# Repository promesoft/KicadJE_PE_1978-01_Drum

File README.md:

# KicadJE_PE_1978-01_Drum
Based on https://worldradiohistory.com/UK/Practical-Electronics/70s/Practical-Electronics-1978-01.pdf

# Purpose

## Board 1 - Drum module
Adjustment:  
Mix of snare amt

Gate Input:  
TTL Square

Output Audio:  
+/- 10V AC coupled

## Board 2 - Breadboard helper
Testing out text prints

Adjustment:  
100k Pot to pinheader  
Push button to pinheader

Input/Output:  
3,5mm jack to pinheader  
+-12V from Eurorack 10pin IDC to breadboard pinheaders

## Board 3 - Desktop PDU for Eurojack
Banana jack in  
16 pin Euro power out

# Status - Being assembled
## Initial 
| Stage  | Detail | Status |
| ------------- | ------------- | ------------- |
| create material  | sch | done |
| | pcb | done |
| | gerber | done |
| production  |   | delivered |
|  | produced | delivered |
|  | delivered | ok |
## Preliminary validation
| Test  | Detail | Status |
| ------------- | ------------- | ------------- |
| Initial Inspection | PDU | ok mechanical|
| Initial Inspection | BB Helper | ok mechanical - Solder-mask-expansion on copper looks best - better than silk |
| Initial Inspection | Drum Module |  |
| Initial Technical Test | Board 1 |  |
| Initial Product Test | Board1 |  |

## Secondary validation
| Test  | Detail | Status |
| ------------- | ------------- |------------- |
| Product Test | 1 | |
| Quality | 1 | |
| Long Term Product Test |  |  |
| Power Draw |  | 

## Errata
### Errata - BB Power
### Errata - PDU
R405 not connected to GND

## Issues and Notes
### 

# Pictures

# Schematic
## Sch 1

# Analysis
## Diag 1

https://worldradiohistory.com/UK/Practical-Electronics/70s/Practical-Electronics-1978-01.pdf

## Prototype

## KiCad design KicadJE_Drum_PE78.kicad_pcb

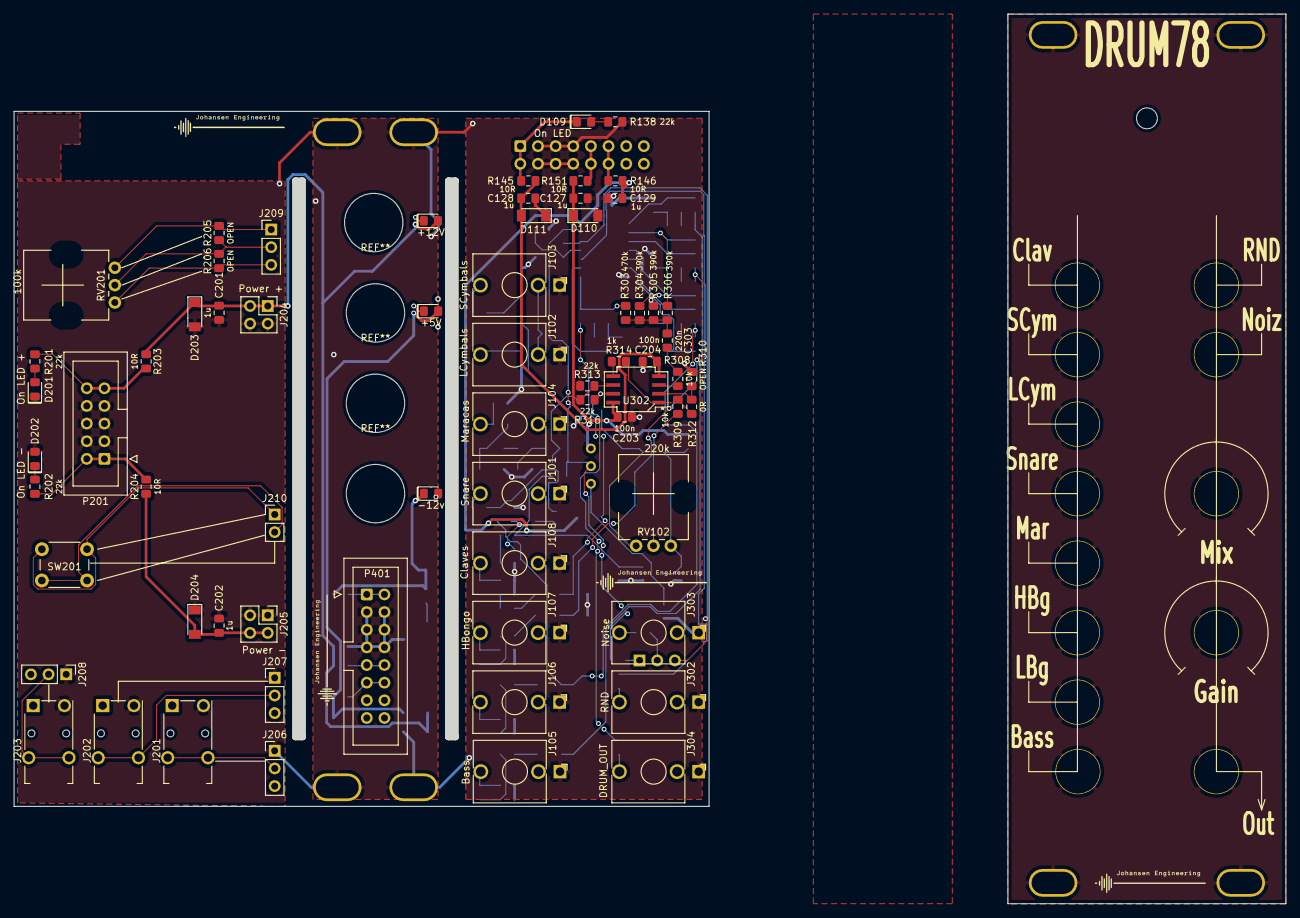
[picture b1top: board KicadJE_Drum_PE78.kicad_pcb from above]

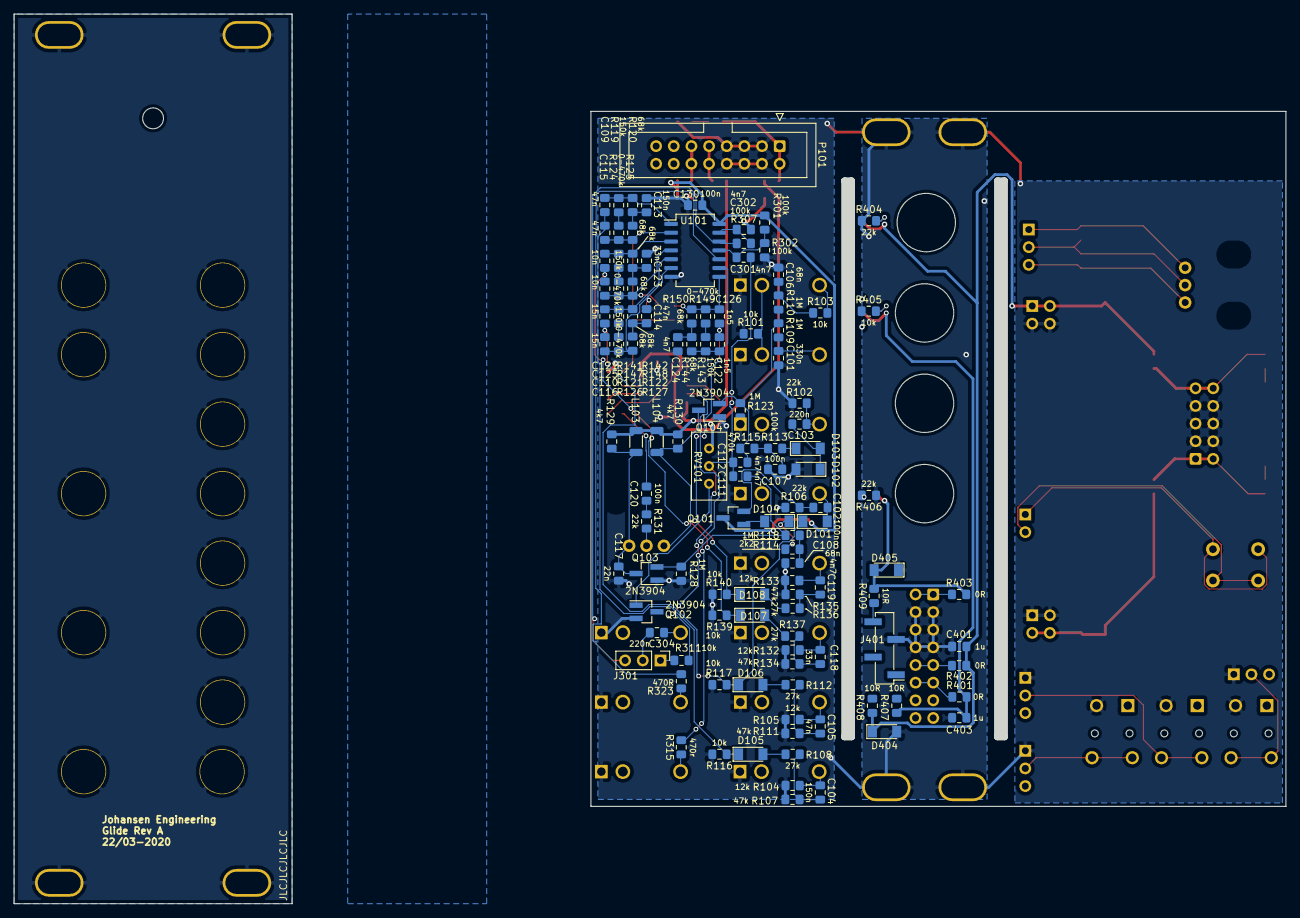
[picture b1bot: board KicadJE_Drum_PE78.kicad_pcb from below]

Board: 2 copper layers, 100.0 x 100.0 mm, 203 parts (121 on the bottom side), 100 nets.

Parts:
C101: 330n; C_0805_AJ
C102, C107, C120, C130, C203, C204: 100n; C_0805_AJ
C103, C303, C304: 220n; C_0805_AJ
C104, C113: 150n; C_0805_AJ
C105, C109, C114, C115: 47n; C_0805_AJ
C106, C108: 68n; C_0805_AJ
C110, C116: 15n; C_0805_AJ
C111, C112, C119, C124, C301, C302: 4n7; C_0805_AJ
C117: 22n; C_0805_AJ
C118, C123: 33n; C_0805_AJ
C121, C125: 10n; C_0805_AJ
C122, C126: 1n5; C_0805_AJ
C127, C128, C129, C201, C202, C401, C403: 1u; C_0805_AJ
D101, D102, D103, D104, D105, D106, D107, D108: 1N4148; D_MiniMELF
D109: On LED; D_0805_AJ
D110, D111, D203, D204, D404, D405: 1N4007; D_MiniMELF
D201: On LED +; D_0805_AJ
D202: On LED -; D_0805_AJ
D401: +12V; D_0805_AJ
D402: +5V; D_0805_AJ
D403: -12v; D_0805_AJ
H101: ON; LED_Hole_3mm
H102, H103, H103#2, H103#3, H103#4, H103#5, H104, H105: MountingHole_Pad; MountingHole_Eurorack3
J101: Snare; Jack_3.5mm_QingPu_WQP-PJ398SM_Vertical_CircularHoles
J102: LCymbals; Jack_3.5mm_QingPu_WQP-PJ398SM_Vertical_CircularHoles
J103: SCymbals; Jack_3.5mm_QingPu_WQP-PJ398SM_Vertical_CircularHoles
J104: Maracas; Jack_3.5mm_QingPu_WQP-PJ398SM_Vertical_CircularHoles
J105: Bass; Jack_3.5mm_QingPu_WQP-PJ398SM_Vertical_CircularHoles
J106: LBongo; Jack_3.5mm_QingPu_WQP-PJ398SM_Vertical_CircularHoles
J107: HBongo; Jack_3.5mm_QingPu_WQP-PJ398SM_Vertical_CircularHoles
J108: Claves; Jack_3.5mm_QingPu_WQP-PJ398SM_Vertical_CircularHoles
J201, J202, J203: AudioJack2_SwitchT; Jack_3.5mm_Switronic_ST-005-G_horizontal
J204: Power +; PinHeader_2x02_P2.54mm_Vertical
J205: Power -; PinHeader_2x02_P2.54mm_Vertical
J206, J207, J208, J209: Conn_01x03_Male; PinHeader_1x03_P2.54mm_Vertical
J210: Conn_01x02_Male; PinHeader_1x02_P2.54mm_Vertical
J301: Tone/Noise; PinHeader_1x03_P2.54mm_Vertical
J302: RND; Jack_3.5mm_QingPu_WQP-PJ398SM_Vertical_CircularHoles
J303: Noise; Jack_3.5mm_QingPu_WQP-PJ398SM_Vertical_CircularHoles
J304: DRUM_OUT; Jack_3.5mm_QingPu_WQP-PJ398SM_Vertical_CircularHoles
J401: Tone/Noise; PinHeader_1x04_P2.54mm_Vertical_SMD_Pin1Left
L103, L104: 100mH; L_1206_3216Metric
P101, P401: HEADER_2x8_Doepfer; IDC-Header_2x08_P2.54mm_Vertical
P201: HEADER_2x5_Doepfer; IDC-Header_2x05_P2.54mm_Vertical
Q101, Q102, Q103, Q104: 2N3904; SOT-23_Handsoldering
R101, R103, R116, R117, R139, R140, R308, R309, R311, R405: 10k; R_0805_AJ
R102, R106, R131, R138, R201, R202, R313, R316, R404, R406: 22k; R_0805_AJ
R104, R105, R132, R133: 12k; R_0805_AJ
R107, R108, R134, R135: 47k; R_0805_AJ
R109, R110, R118, R123, R128: 1M; R_0805_AJ
R111, R112, R136, R137: 27k; R_0805_AJ
R113, R301, R302, R307: 100k; R_0805_AJ
R114: 2k2; R_0805_AJ
R115, R303: 470k; R_0805_AJ
R119, R121, R141, R143: 150k; R_0805_AJ
R120, R122, R125, R127, R142, R144, R148, R150: 68k; R_0805_AJ
R124, R126, R147, R149: 0-470k; R_0805_AJ
R129, R130: 4k7; R_0805_AJ
R145, R146, R151, R203, R204, R407, R408, R409: 10R; R_0805_AJ
R205, R206, R310: OPEN; R_0805_AJ
R304, R305, R306: 390k; R_0805_AJ
R312, R401, R402, R403: 0R; R_0805_AJ
R314: 1k; R_0805_AJ
R315: 470r; R_0805_AJ
R323: 470R; R_0805_AJ
RV101: R_POT_TRIM; Potentiometer_Bourns_3296W_Vertical
RV102: 220k; Potentiometer_China_RK09_Single_Vertical_AJ
RV201: 100k; Potentiometer_China_RK09_Single_Vertical_AJ
SW201: SW_SPDT; SW_PUSH_6mm_H8mm
TP102: SQ; Jack_6m3
TP103: In1; Jack_6m3
TP105, TP105#2, TP105#3, TP105#4, TP105#5, TP105#6: In3; Jack_6m3
TP106: HS; Jack_6m3
TP107: OFF1; Pot_6m3_scale1
TP107#2: FM; Jack_6m3
TP108: PWM; Jack_6m3
TP112: Fine; Pot_6m3_scale1
U101: 74HC04; SO-14_5.3x10.2mm_P1.27mm
U302: TL072; AJ_SO-8_5.3x6.2mm_P1.27mm

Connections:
+5V: C129.1, C130.1, C403.1, D402.2, Q101.3, R146.1, R301.1, R401.2, R407.2, U101.14
+12Vc: C127.1, C201.1, C203.1, C401.1, D110.1, D203.1, D401.2, D404.1, J204.1, J204.3, L103.1, L104.1, R129.2, R130.2, R151.1, R203.1, R402.2, R408.2, RV101.1, U302.8
-12Vc: C128.2, C202.2, C204.2, D111.2, D204.2, D403.1, D405.2, J205.2, J205.4, R145.1, R204.1, R403.2, R409.2, U302.4
/+5: P101.11, P101.12, R146.2
/+12: P101.9, P101.10, R151.2
/-12: D109.1, P101.1, P101.2, R145.2
/Breadboard_extender/+12: P201.9, P201.10, R201.1, R203.2
/Breadboard_extender/-12: P201.1, P201.2, R202.1, R204.2
/KicadJE_PDU_1/+5: P401.11, P401.12, R401.1
/KicadJE_PDU_1/+12: P401.9, P401.10, R402.1
/KicadJE_PDU_1/-12: P401.1, P401.2, R403.1
BassOut: C115.1, R124.1, R125.1, R306.2, U101.2
BassTrig: C109.1, C115.2, D105.1, R116.1
ClavesOut: C126.1, R149.1, R150.1, R303.2, U101.8
ClavesTrig: C122.1, C126.2, D108.1, R140.1
GND: C101.2, C106.2, C107.2, C108.2, C113.2, C114.2, C117.2, C123.2, C124.2, C127.2, C128.1, C129.2, C130.2, C201.2, C202.1, C203.2, C204.1, C302.1, C401.2, C403.2, D102.2, D110.2, D111.1, D201.1, D202.2, D203.2, D204.1, D404.2, D405.1, H102.1, H103.1, H103#2.1, H103#3.1, H103#4.1, H103#5.1, H104.1, H105.1, J101.S, J102.S, J103.S, J104.S, J105.S, J106.S, J107.S, J108.S, J201.S, J202.S, J203.S, J204.2, J204.4, J205.1, J205.3, J206.1, J207.1, J208.1, J302.S, J303.S, J304.S, J401.3, P101.3, P101.4, P101.5, P101.6, P101.7, P101.8, P201.3, P201.4, P201.5, P201.6, P201.7, P201.8, P401.3, P401.4, P401.5, P401.6, P401.7, P401.8, Q102.2, Q103.1, Q104.1, R101.1, R102.2, R104.2, R105.2, R106.2, R107.2, R108.2, R116.2, R117.2, R123.1, R128.1, R132.2, R133.2, R134.2, R135.2, R138.1, R139.2, R140.2, R302.2, R310.2, R313.1, R404.1, R405.1, R406.1, TP102.1, TP103.1, TP105.1, TP105#2.1, TP105#3.1, TP105#4.1, TP105#5.1, TP105#6.1, TP106.1, TP107.1, TP107#2.1, TP108.1, TP112.1, U101.7
HBongoOut: C125.1, R147.1, R148.1, R304.2, U101.4
HBongoTrig: C121.1, C125.2, D107.1, R139.1
LBongoOut: C116.1, R126.1, R127.1, R305.2, U101.6
LBongoTrig: C110.1, C116.2, D101.1, D106.1, R117.1
NDrumsOut: C120.2, R309.2
unnamed: C101.1, J102.T, R109.2
unnamed: C102.1, D101.2, J101.T
unnamed: C102.2, Q101.2, R106.1
unnamed: C103.1, J104.T, R102.1
unnamed: C103.2, D102.1, D103.2
unnamed: C104.1, J105.T, R104.1
unnamed: C104.2, R107.1, R111.2
unnamed: C105.1, J106.T, R105.1
unnamed: C105.2, R108.1, R112.2
unnamed: C106.1, R103.1, R110.2
unnamed: C107.1, R113.1, R115.2
unnamed: C108.1, R114.1, R118.2
unnamed: C109.2, R119.2, R120.2, U101.1
unnamed: C110.2, R121.2, R122.2, U101.5
unnamed: C111.2, Q103.2, R118.1, R128.2
unnamed: C112.1, Q104.2, R109.1, R110.1, R115.1, R123.2
unnamed: C113.1, R120.1, R125.2
unnamed: C114.1, R122.1, R127.2
unnamed: C117.1, L103.2, Q103.3, R129.1, RV102.1
unnamed: C118.1, J107.T, R132.1
unnamed: C118.2, R134.1, R137.2
unnamed: C119.1, J108.T, R133.1
unnamed: C119.2, R135.1, R136.2
unnamed: C120.1, R131.1
unnamed: C121.2, R141.2, R142.2, U101.3
unnamed: C122.2, R143.2, R144.2, U101.9
unnamed: C123.1, R142.1, R148.2
unnamed: C124.1, R144.1, R150.2
unnamed: C301.1, R301.2, R302.1, U101.11
unnamed: C302.2, R307.2, U101.13
unnamed: C303.1, R308.2
unnamed: C303.2, R303.1, R304.1, R305.1, R306.1
unnamed: C304.1, J303.T
unnamed: C304.2, J301.2
unnamed: D103.1, R113.2
unnamed: D104.1, R114.2
unnamed: D104.2, Q101.1
unnamed: D105.2, R111.1
unnamed: D106.2, R112.1
unnamed: D107.2, R137.1
unnamed: D108.2, R136.1
unnamed: D109.2, R138.2
unnamed: D201.2, R201.2
unnamed: D202.1, R202.2
unnamed: D401.1, R404.2
unnamed: D402.1, R405.2
unnamed: D403.2, R406.2
unnamed: J102.TN, J103.TN, R101.2
unnamed: J103.T, R103.2
unnamed: J201.T, J206.2
unnamed: J202.T, J207.2
unnamed: J203.T, J208.2
unnamed: J209.1, R205.2, RV201.1
unnamed: J209.2, R205.1, R206.2, RV201.2
unnamed: J209.3, R206.1, RV201.3
unnamed: J210.1, SW201.1
unnamed: J210.2, SW201.2
unnamed: J301.1, R311.2
unnamed: J301.3, R307.1, U101.12
unnamed: J302.T, R323.1
unnamed: J304.T, R315.1
unnamed: J401.1, R407.1
unnamed: J401.2, R408.1
unnamed: J401.4, R409.1
unnamed: L104.2, Q104.3, R130.1, RV102.3
unnamed: Q102.1, RV101.3
unnamed: R119.1, R124.2
unnamed: R121.1, R126.2
unnamed: R131.2, RV102.2
unnamed: R141.1, R147.2
unnamed: R143.1, R149.2
unnamed: R308.1, U302.3
unnamed: R309.1, R312.1, R314.2, U302.1
unnamed: R310.1, R312.2, U302.2
unnamed: R313.2, R316.1, U302.6
unnamed: R314.1, U302.5
unnamed: R315.2, R316.2, U302.7
unnamed: R323.2, U101.10
NoiseOut: C111.1, C112.2, C301.2, R311.1, RV101.2

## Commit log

2021-03-17 Project started
2021-03-17 init sch
2021-04-14 Drum sheet started
2021-04-18 Breadboard sch
2021-04-19 Sinus osc done - sch
2021-04-20 Noise drums
2021-04-20 Amp out
2021-04-21 sch amp
2021-04-21 Update misc diags
2021-04-21 Annotate
2021-04-21 ERC Performed - changed symbol for 16pin pwr
2021-04-21 Footprint adj
2021-04-21 Faceplate
2021-04-22 Faceplate etc
2021-04-22 BB Power
2021-04-22 Powerfootprintupdated
2021-04-22 3D upd
2021-04-26 AC coupled noise
2021-04-26 Power to TL072
2021-04-26 THT Coils removed
2021-04-26 Components initially placed
2021-04-26 Schematic pictures
2021-04-27 Breadboard routed
2021-04-27 decoupling for Op Amp
2021-04-27 BB Logo - GND planes
2021-04-27 PDU unit added
2021-04-27 Front Component Silk
2021-04-27 Labels back
2021-04-27 Board labels
2021-04-28 Doc and backside
2021-04-28 Prep for different gerber
2021-04-28 Faceplate + Gerber
2021-04-28 Base
2021-04-28 Base-Gerber
2021-04-28 Faceplate - not matching base - fix
2021-04-28 base removed from face pcb
2021-04-28 Face tweaked
2021-04-28 Face Gerber
2021-04-28 Gerber Face
2021-05-02 misc
2021-05-11 Fix PCB Errors
